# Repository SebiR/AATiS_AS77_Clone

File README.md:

# AATiS DCF77 Empfänger

This is a clone of the original AATiS AS77 DCF77 Receiver board.

This project was the very first electronic kit that I assembled when I was eleven or twelve years old and it basically started my career as an EE.\
The receiver I built back then still functions to this day and as the design itself celebrates its 30th birthday in this year, I wanted to preserve it for generations to come as the original PCB has been discontinued.

This is a really great project for beginners to learn soldering and learn something about analog circuits and DCF77.

## Description

* Mechanical 99.9% identical to the original board
* Layout 99.9% identical to original layout

In case you're wondering: The layout looks a bit strange, but I think it was designed with a really simple CAD software in 1994.
But the layout is great if you want to etch the PCB yourself!

## Status Quo
* Layout basically finished
* Schematic still a mess
* Library needs cleaning up

## Disclaimer
> [!CAUTION]
> This project was created to archive and preserve the DCF77 receiver. AATis/Helmut Pape own all the rights to this design.
> There's no copyright infringement intended, please contact me for removal.

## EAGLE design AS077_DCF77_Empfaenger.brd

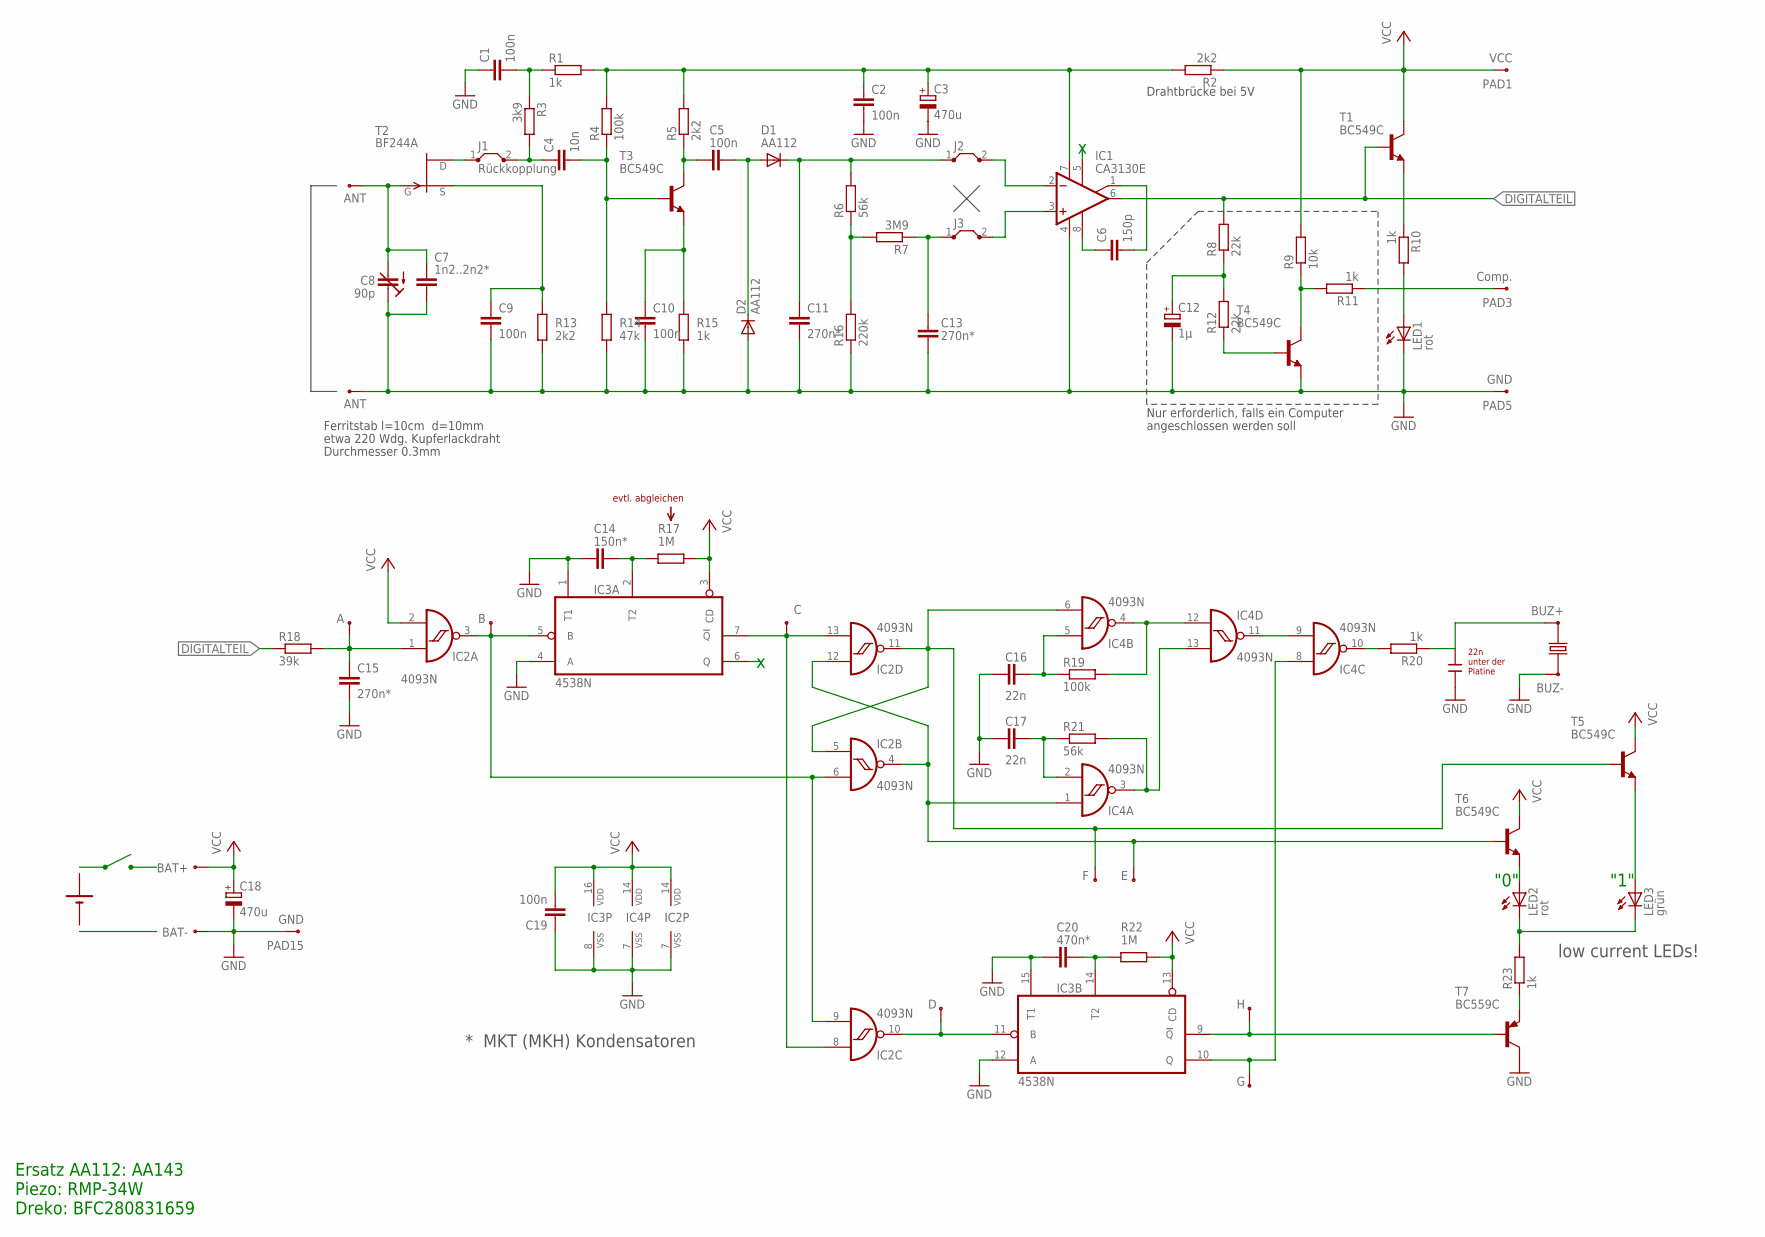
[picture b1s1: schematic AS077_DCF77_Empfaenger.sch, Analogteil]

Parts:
C1, C2, C5, C9, C10, C19: 100n; RCL_C050-024X044
C3, C18: 470u; RCL_E5-10,5
C4: 10n; RCL_C050-024X044
C6: 150p; RCL_C050-024X044
C7: 1n2..2n2*; RCL_C075-032X103
C8: 90p; RCL_CTRIM808-BC7.5
C11, C13, C15: 270n*; RCL_C075-032X103
C12: 1µ; E5-6
C14: 150n*; RCL_C075-032X103
C16, C17: 22n; RCL_C050-024X044
C20: 470n*; RCL_C075-032X103
D1, D2: AA112; DIODE_DO07
IC1: CA3130E; DIL08
IC2, IC4: 4093N; DIL14
IC3: 4538N; DIL16
J1: Rückkopplung; JUMPER_05
J2, J3: JUMPER_J5MM; JUMPER_05
LED1, LED2: rot; LED_LED5MM
LED3: grün; LED_LED5MM
PAD1: VCC; WIREPAD_2.2/1.3
PAD2, PAD4: ANT; WIREPAD_2.2/1.3
PAD3: Comp.; WIREPAD_2.2/1.3
PAD5, PAD15: GND; WIREPAD_2.2/1.3
PAD6: A; WIREPAD_2.2/1.3
PAD7: B; WIREPAD_2.2/1.3
PAD8: C; WIREPAD_2.2/1.3
PAD9: BUZ-; WIREPAD_2.2/1.3
PAD10: BUZ+; WIREPAD_2.2/1.3
PAD11: BAT+; WIREPAD_2.2/1.3
PAD12: F; WIREPAD_2.2/1.3
PAD13: E; WIREPAD_2.2/1.3
PAD14: BAT-; WIREPAD_2.2/1.3
PAD16: D; WIREPAD_2.2/1.3
PAD17: H; WIREPAD_2.2/1.3
PAD18: G; WIREPAD_2.2/1.3
Q1: 34MM_PIEZO; 34MM_PIEZO_SCREW
R1, R10, R11, R15, R20: 1k; RCL_0207/5V
R2, R5, R13: 2k2; RCL_0207/5V
R3: 3k9; RCL_0207/15
R4, R19: 100k; RCL_0207/5V
R6, R21: 56k; RCL_0207/5V
R7: 3M9; RCL_0207/5V
R8, R12: 22k; RCL_0207/5V
R9: 10k; RCL_0207/5V
R14: 47k; RCL_0207/5V
R16: 220k; RCL_0207/5V
R17, R22: 1M; RCL_0207/15
R18: 39k; RCL_0207/15
R23: 1k; RCL_0207/10
T1, T3, T4: BC549C; TO92_5.08
T2: BF244A; TO92_5.08
T5, T6: BC549C; TO92_2.54
T7: BC559C; TO92_5.08
U$1: 9V_SILKSCREEN; 9V_BLOCK

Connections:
DIGITALTEIL: IC1.6 (OUT), R8.2, R18.1, T1.2 (B)
GND: C1.1, C2.2, C3.-, C7.2, C8.1 (E), C8.3 (E), C9.2, C10.2, C11.2, C12.-, C13.2, C14.1, C15.2, C16.1, C17.1, C18.-, C19.1, C20.1, D2.A, IC1.4 (V-), IC2.7 (VSS), IC3.1 (T1), IC3.4 (A), IC3.8 (VSS), IC3.12 (A), IC3.15 (T1), IC4.7 (VSS), LED1.K (C), PAD4.1, PAD5.1, PAD9.1, PAD14.1, PAD15.1, R13.1, R14.1, R15.1, R16.1, T4.3 (E), T7.1 (C)
unnamed: IC1.3 (+IN), J3.2
unnamed: IC1.2 (-IN), J2.2
unnamed: C13.1, J3.1, R7.1
unnamed: R6.1, R7.2, R16.2
unnamed: C11.1, D1.C, J2.1, R6.2
unnamed: C5.2, D1.A, D2.C
unnamed: C6.1, IC1.8 (CMP)
unnamed: C10.1, R15.2, T3.3 (E)
unnamed: C5.1, R5.1, T3.1 (C)
unnamed: C4.2, R4.1, R14.2, T3.2 (B)
unnamed: C2.1, C3.+, IC1.7 (V+), R1.2, R2.2, R4.2, R5.2
unnamed: C1.2, R1.1, R3.1
unnamed: C4.1, J1.2, R3.2
unnamed: J1.1, T2.3 (D)
unnamed: C9.1, R13.2, T2.1 (S)
unnamed: C6.2, IC1.1 (ON/CMP)
unnamed: PAD10.1, R20.1
unnamed: C7.1, C8.2 (A), PAD2.1, T2.2 (G)
unnamed: C20.2, IC3.14 (T2), R22.2
unnamed: C12.+, R8.1, R12.2
unnamed: PAD3.1, R11.1
unnamed: R12.1, T4.2 (B)
unnamed: R9.1, R11.2, T4.1 (C)
unnamed: LED1.A, R10.2
unnamed: R10.1, T1.3 (E)
unnamed: C15.1, IC2.1 (I0), PAD6.1, R18.2
unnamed: IC2.8 (I0), IC2.13 (I1), IC3.7 (!Q), PAD8.1
unnamed: IC2.5 (I0), IC2.11 (O), IC4.6 (I1), PAD12.1, T5.2 (B)
unnamed: IC4.4 (O), IC4.12 (I0), R19.2
unnamed: IC2.3 (O), IC2.6 (I1), IC2.9 (I1), IC3.5 (B), PAD7.1
unnamed: IC2.10 (O), IC3.11 (B), PAD16.1
unnamed: IC2.4 (O), IC2.12 (I0), IC4.1 (I0), PAD13.1, T6.2 (B)
unnamed: IC4.3 (O), IC4.13 (I1), R21.2
unnamed: IC4.9 (I1), IC4.11 (O)
unnamed: C16.2, IC4.5 (I0), R19.1
unnamed: C17.2, IC4.2 (I1), R21.1
unnamed: C14.2, IC3.2 (T2), R17.2
unnamed: IC3.10 (Q), IC4.8 (I0), PAD18.1
unnamed: IC3.9 (!Q), PAD17.1, T7.2 (B)
unnamed: R23.1, T7.3 (E)
unnamed: LED2.A, T6.3 (E)
unnamed: LED3.A, T5.3 (E)
unnamed: LED2.K (C), LED3.K (C), R23.2
unnamed: IC4.10 (O), R20.2
VCC: C18.+, C19.2, IC2.2 (I1), IC2.14 (VDD), IC3.3 (CD), IC3.13 (CD), IC3.16 (VDD), IC4.14 (VDD), PAD1.1, PAD11.1, R2.1, R9.2, R17.1, R22.1, T1.1 (C), T5.1 (C), T6.1 (C)

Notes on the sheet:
angeschlossen werden soll
Nur erforderlich, falls ein Computer
Ferritstab l=10cm d=10mm
etwa 220 Wdg. Kupferlackdraht
Durchmesser 0.3mm
Drahtbrücke bei 5V
Ersatz AA112: AA143 Piezo: RMP-34W Dreko: BFC280831659
"0"
"1"
* MKT (MKH) Kondensatoren
low current LEDs!
22n unter der Platine
evtl. abgleichen

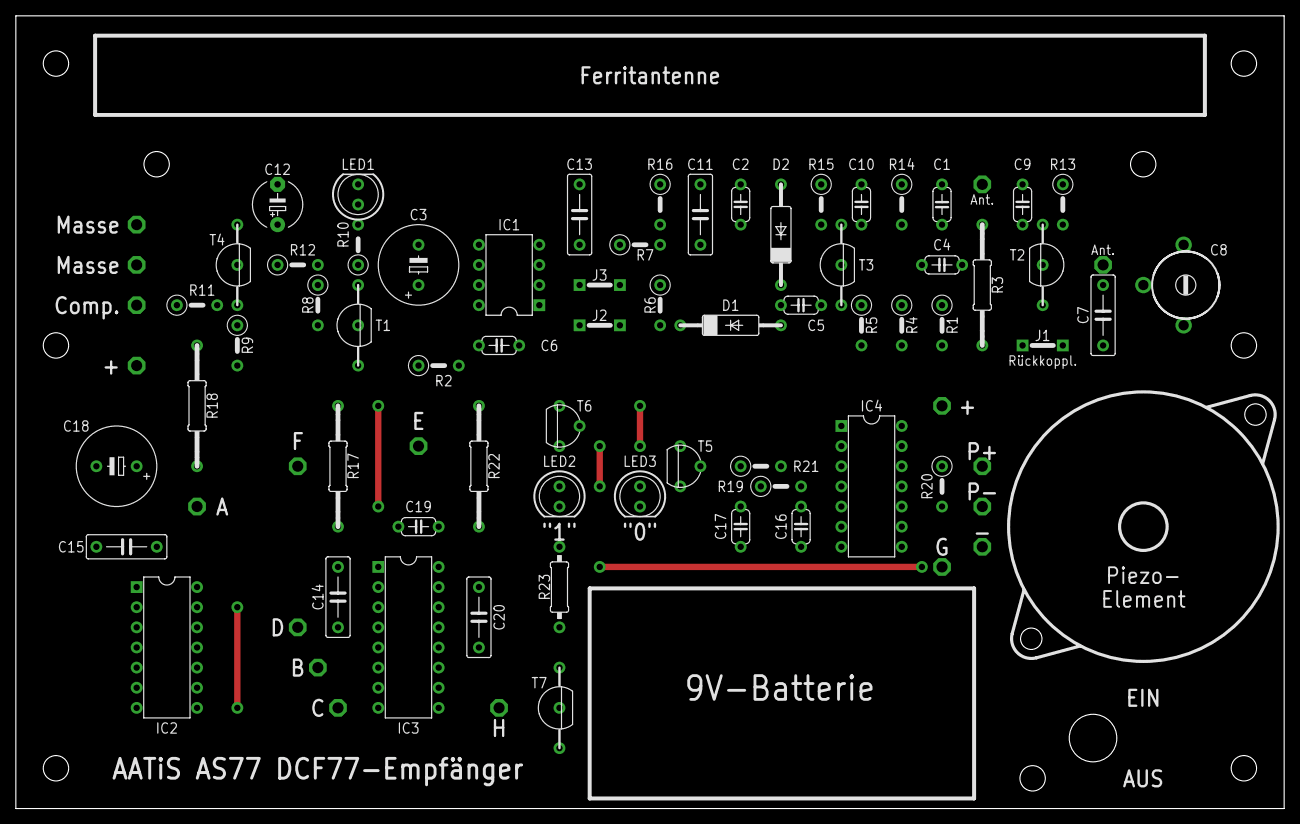
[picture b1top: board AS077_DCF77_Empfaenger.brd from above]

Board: 2 copper layers, 160.0 x 100.0 mm, 82 parts (0 on the bottom side), 47 nets.

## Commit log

2024-07-18 * Added "bottom capacitor" * Added nets and polygons to not connected IC pins
2024-07-18 * Added more details to the silkscreen * Fixed all Values in schematic
2024-07-18 * Updated PCB renderings
2024-07-18 * more silkscreen improvements * added GERBER
2024-07-19 * Updated and cleaned up the library * Cleaned up the schematic * Renumbered all parts * Updated images, gerbers and schematic pdf * Added small arduino test script for decoding
2024-07-19 Change some components
2024-07-19 * Renamed included library * Changed all references to new lib name
2024-07-19 * More schematic and layout cleanup
2024-07-19 Updated production an documentation files
2024-07-19 fixed filename
2024-07-19 Minor Fixes
2024-12-26 updated LBR and BRD: Solder pin holes are now 1.4mm drills instead of 1.3
2025-01-19 * Updated test pin hole diameter also in BRD and GERBER (only updated LBR before)
